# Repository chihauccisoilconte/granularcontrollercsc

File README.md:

# granularcontrollercsc

This repository contains all the documentation and all the materials that are necessary to build the "Granular controller".
The Granular Contrller was designed and built in 2021 as part of the computer music (informatica per la musica e multimedia) course of University of Padua.

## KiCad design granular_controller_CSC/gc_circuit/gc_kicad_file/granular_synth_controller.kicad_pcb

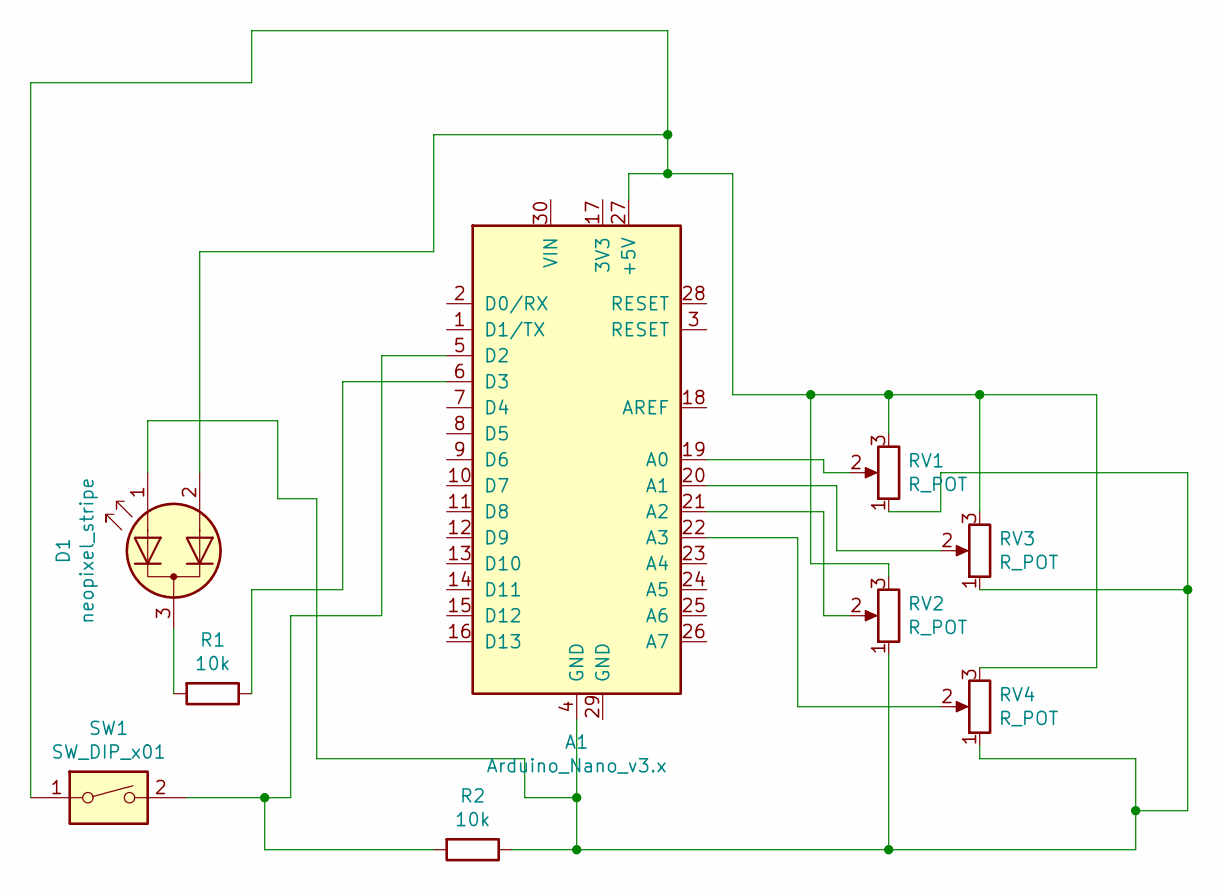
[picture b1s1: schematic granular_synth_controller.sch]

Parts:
A1: Arduino_Nano_v3.x; Arduino_Nano
D1: neopixel_stripe; FanPinHeader_1x03_P2.54mm_Vertical
R1, R2: 10k; R_Axial_DIN0309_L9.0mm_D3.2mm_P12.70mm_Horizontal
RV1, RV2, RV3, RV4: R_POT; FanPinHeader_1x03_P2.54mm_Vertical
SW1: SW_DIP_x01; MagneticBuzzer_CUI_CST-931RP-A

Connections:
unnamed: A1.4 (GND), D1.1 (A1), R2.1, RV1.1, RV2.1, RV3.1, RV4.1
unnamed: A1.5 (D2), R2.2, SW1.2
unnamed: A1.6 (D3), R1.1
unnamed: A1.19 (A0), RV1.2
unnamed: A1.20 (A1), RV3.2
unnamed: A1.21 (A2), RV2.2
unnamed: A1.22 (A3), RV4.2
unnamed: A1.27 (+5V), D1.2 (A2), RV1.3, RV2.3, RV3.3, RV4.3, SW1.1
unnamed: D1.3 (K), R1.2

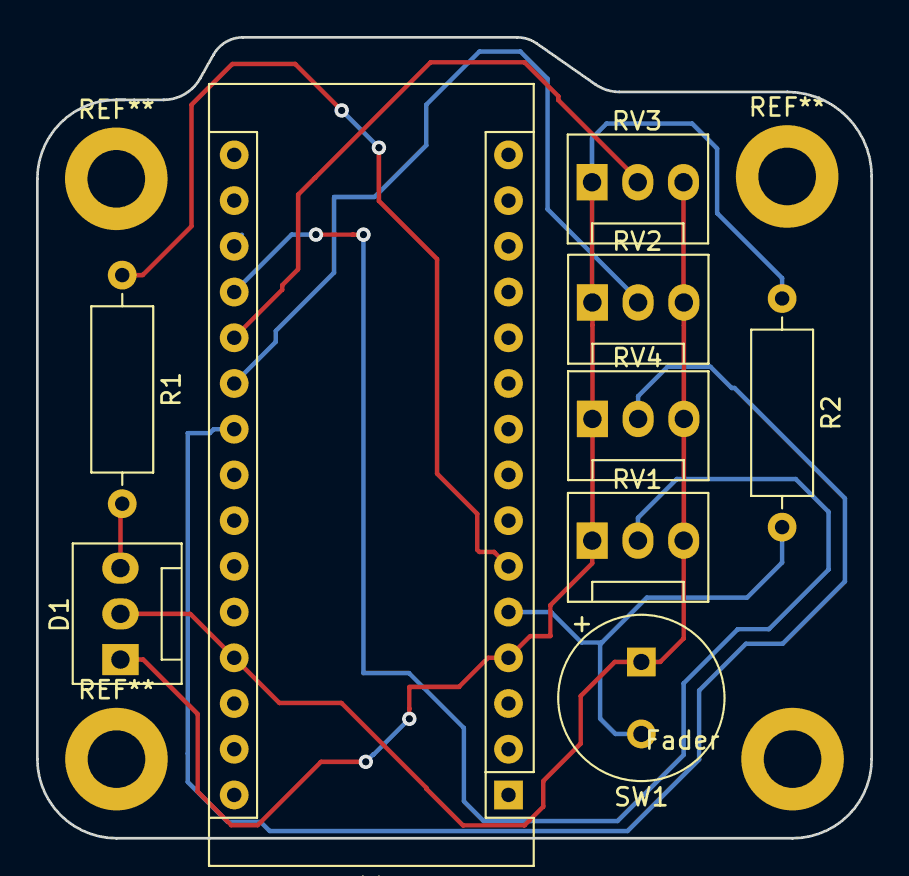
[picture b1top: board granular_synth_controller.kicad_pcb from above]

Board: 2 copper layers, 46.4 x 44.5 mm, 10 parts (0 on the bottom side), 9 nets.

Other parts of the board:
Fader: MountingHole_3.2mm_M3_ISO7380_Pad
